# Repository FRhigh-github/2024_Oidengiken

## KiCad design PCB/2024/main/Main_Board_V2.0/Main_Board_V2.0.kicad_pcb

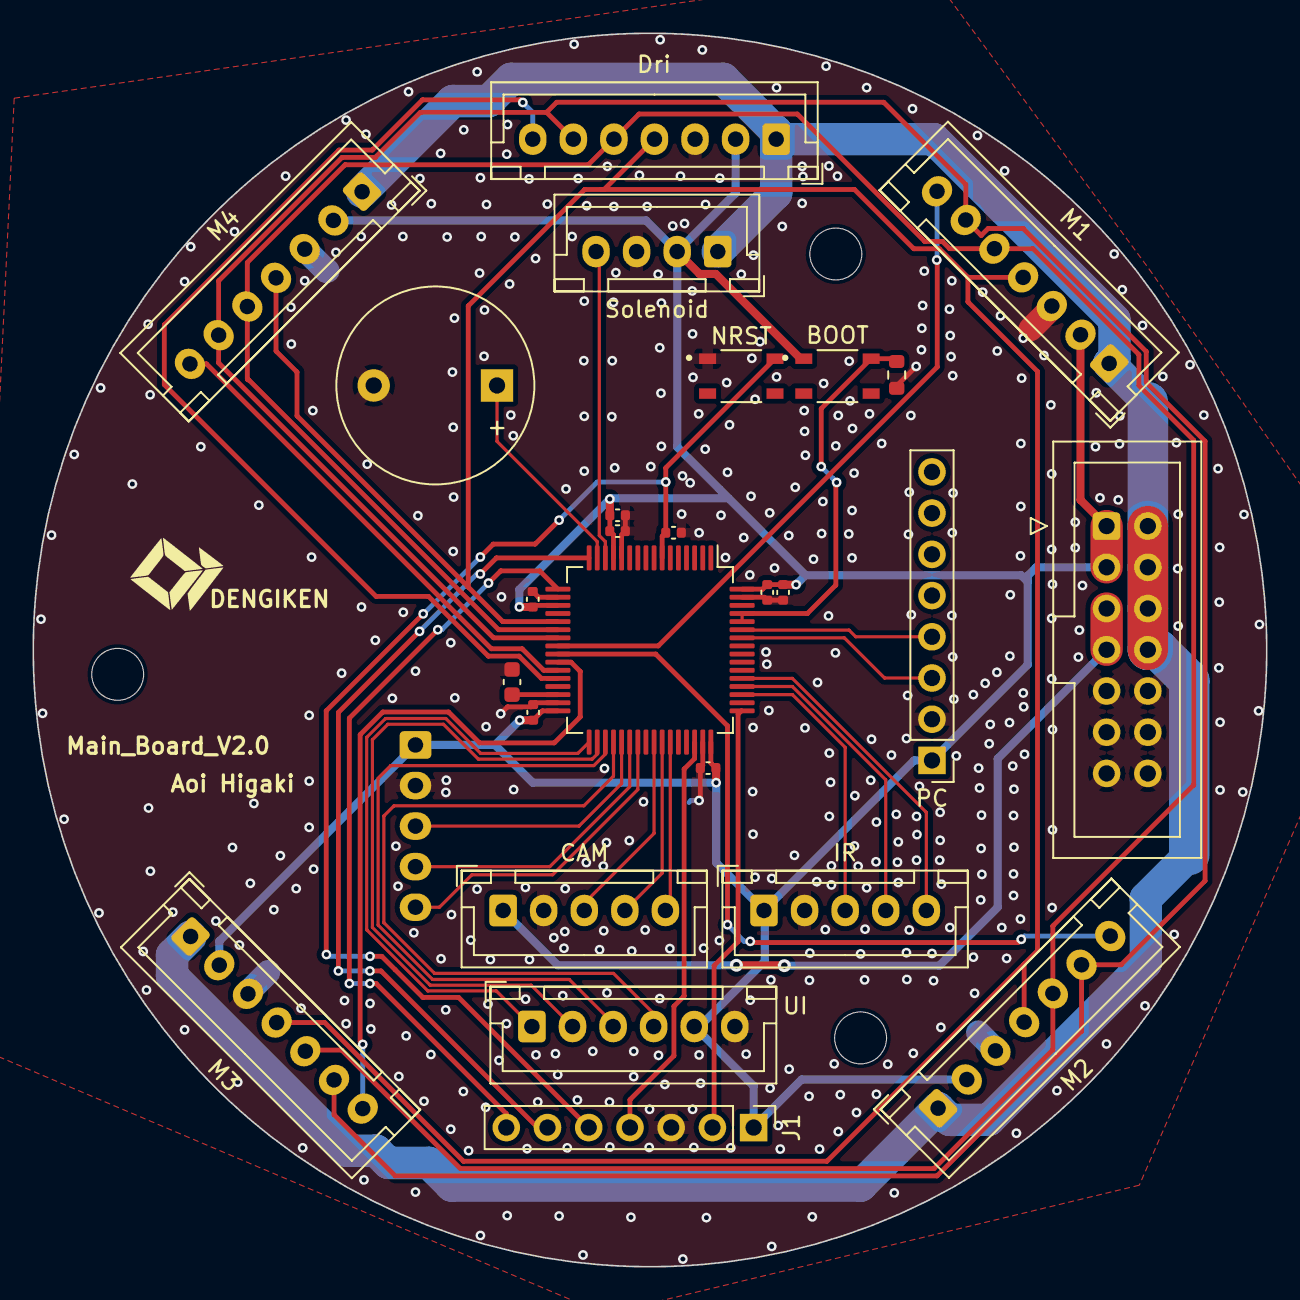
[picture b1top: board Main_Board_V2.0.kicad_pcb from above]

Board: 2 copper layers, 76.0 x 76.0 mm, 27 parts (1 on the bottom side), 36 nets.

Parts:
BOOT: SW_Push; SW_SKRPABE010
BZ1: Buzzer; Buzzer_12x9.5RM7.6
C1, C3, C4, C6, C8, C9: 0.1u; C_0402_1005Metric
C2: 2.2u; C_0603_1608Metric
C5, C7: 1u; C_0402_1005Metric
CAM: CAM; JST_XH_B5B-XH-A_1x05_P2.50mm_Vertical
Dri: dri; JST_XH_B7B-XH-A_1x07_P2.50mm_Vertical
IR: IR; JST_XH_B5B-XH-A_1x05_P2.50mm_Vertical
J1: Conn_01x07_Pin; PinHeader_1x07_P2.54mm_Vertical
J11: 電源基盤; IDC-Header_2x07_P2.54mm_Vertical
Line: Line; JST_XH_B5B-XH-A_1x05_P2.50mm_Vertical
M1: M1; JST_XH_B7B-XH-A_1x07_P2.50mm_Vertical
M2: M2; JST_XH_B7B-XH-A_1x07_P2.50mm_Vertical
M3: M3; JST_XH_B7B-XH-A_1x07_P2.50mm_Vertical
M4: M4; JST_XH_B7B-XH-A_1x07_P2.50mm_Vertical
NRST: SW_Push; SW_SKRPABE010
PC: Conn_01x08_Pin; PinHeader_1x08_P2.54mm_Vertical
R1: 10k; R_0603_1608Metric
Solenoid: Solenoid; JST_XH_B4B-XH-A_1x04_P2.50mm_Vertical
U1: STM32F446RETx; LQFP-64_10x10mm_P0.5mm
UI: UI; JST_XH_B6B-XH-A_1x06_P2.50mm_Vertical

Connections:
+5V: CAM.1, J11.5, J11.7
+12V: Dri.1, J11.2, J11.4, J11.6, J11.8, M1.1, M2.1, M3.1, M4.1, Solenoid.1
BOOT: BOOT.2, R1.1, U1.60 (BOOT0), U1.61 (PB8)
Buzzer: BZ1.1 (-), U1.15 (PA1)
I2C_SCL: PC.3, U1.58 (PB6)
I2C_SDA: PC.4, U1.59 (PB7)
NRST: C9.1, J1.5, NRST.2, U1.7 (NRST)
SPI1_CS0: M1.7, U1.24 (PC4)
SPI1_CS1: M2.7, U1.25 (PC5)
SPI1_CS2: M3.7, U1.26 (PB0)
SPI1_CS3: M4.7, U1.27 (PB1)
SPI1_CS4: Dri.7, U1.28 (PB2)
SPI1_MISO: Dri.5, M1.5, M2.5, M3.5, M4.5, U1.22 (PA6)
SPI1_MOSI: Dri.6, M1.6, M2.6, M3.6, M4.6, U1.23 (PA7)
SPI1_SCK: Dri.4, M1.4, M2.4, M3.4, M4.4, U1.21 (PA5)
ST_SW: U1.33 (PB12), UI.1
SWCLK: J1.2, U1.49 (PA14)
SWDIO: J1.4, U1.46 (PA13)
Solenoid: Solenoid.4, U1.14 (PA0)
UI_1: U1.34 (PB13), UI.2
UI_2: U1.35 (PB14), UI.3
UI_3: U1.36 (PB15), UI.4
USART1_CK: CAM.3, U1.41 (PA8)
USART1_RX: CAM.5, U1.43 (PA10)
USART1_TX: CAM.4, U1.42 (PA9)
USART2_RX: J1.7, U1.17 (PA3)
USART2_TX: J1.6, U1.16 (PA2)
USART3_CK: IR.5, U1.53 (PC12)
USART3_RX: IR.4, U1.52 (PC11)
USART3_TX: IR.3, U1.51 (PC10)
USART6_CK: Line.5, U1.39 (PC8)
USART6_RX: Line.4, U1.38 (PC7)
USART6_TX: Line.3, U1.37 (PC6)
VCAP: C2.1, U1.30 (VCAP_1)
VDD1: BOOT.1, C1.1, C3.1, C4.1, C5.1, C6.1, C7.1, C8.1, Dri.2, IR.1, J1.1, J11.1, J11.3, Line.1, M1.2, M2.2, M3.2, M4.2, PC.1, Solenoid.2, U1.13 (VDDA), U1.19 (VDD), U1.32 (VDD), U1.48 (VDD), U1.64 (VDD), UI.5
VSSA: BZ1.2 (+), C1.2, C2.2, C3.2, C4.2, C5.2, C6.2, C7.2, C8.2, C9.2, CAM.2, Dri.3, IR.2, J1.3, J11.9, J11.10, J11.11, J11.12, J11.13, J11.14, Line.2, M1.3, M2.3, M3.3, M4.3, NRST.1, PC.2, R1.2, Solenoid.3, U1.12 (VSSA), U1.18 (VSS), U1.31 (VSS), U1.47 (VSS), U1.63 (VSS), UI.6

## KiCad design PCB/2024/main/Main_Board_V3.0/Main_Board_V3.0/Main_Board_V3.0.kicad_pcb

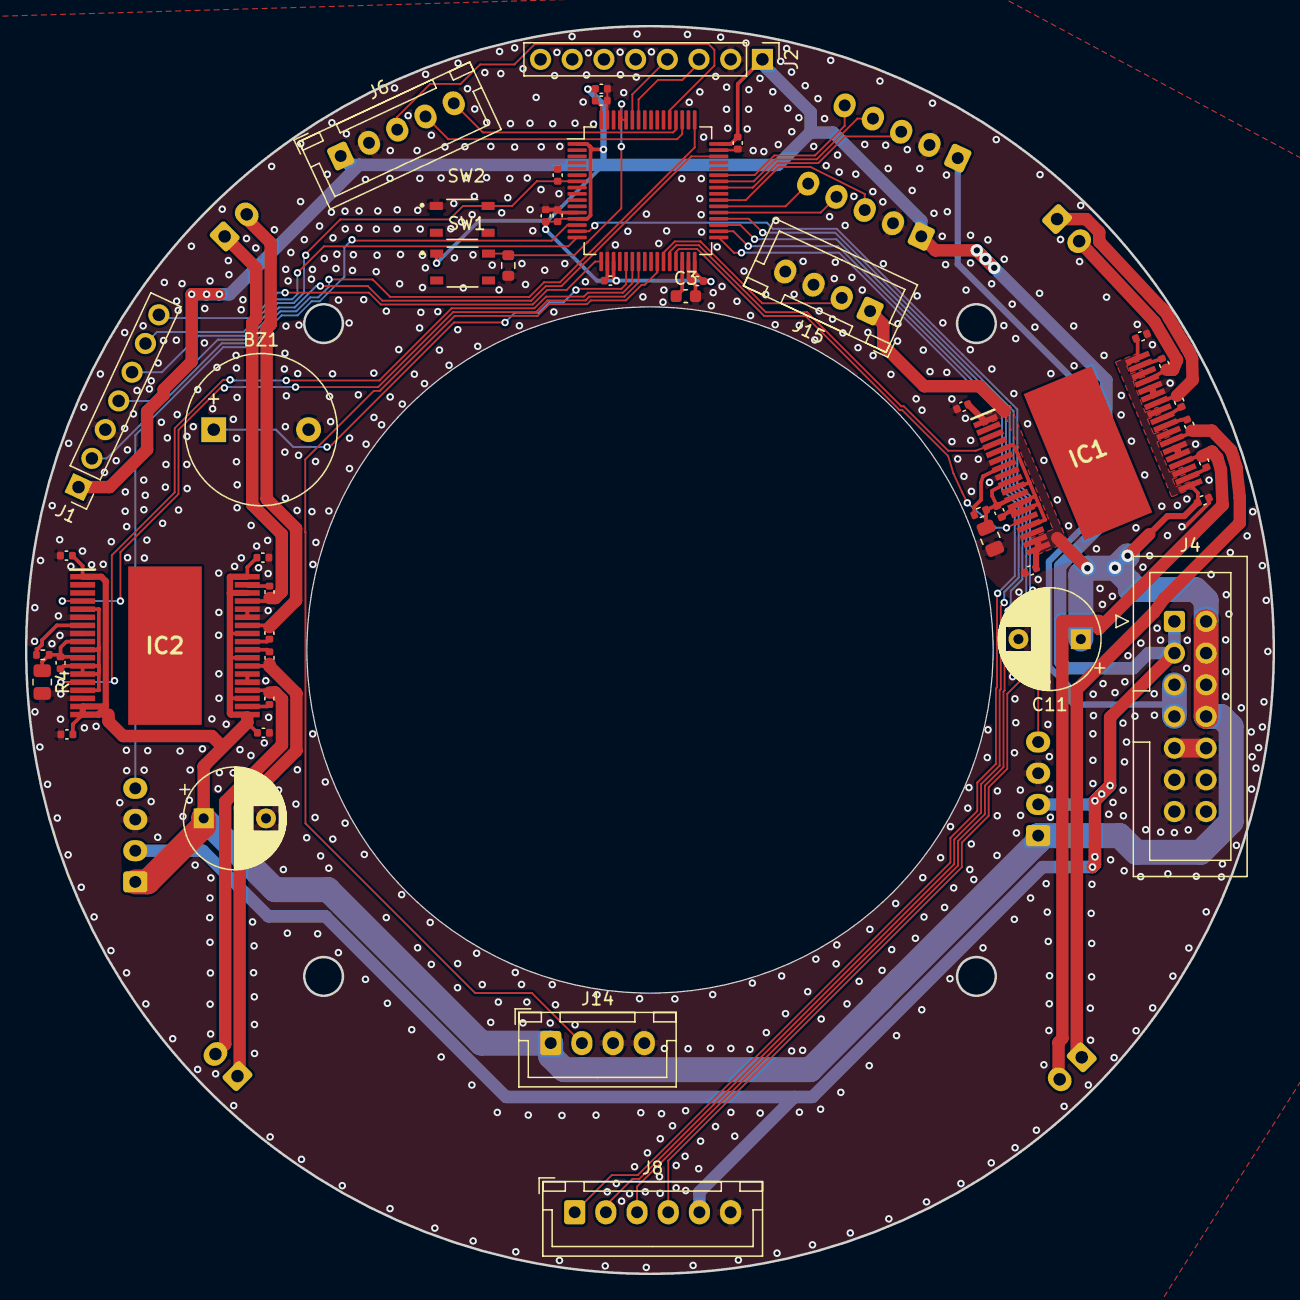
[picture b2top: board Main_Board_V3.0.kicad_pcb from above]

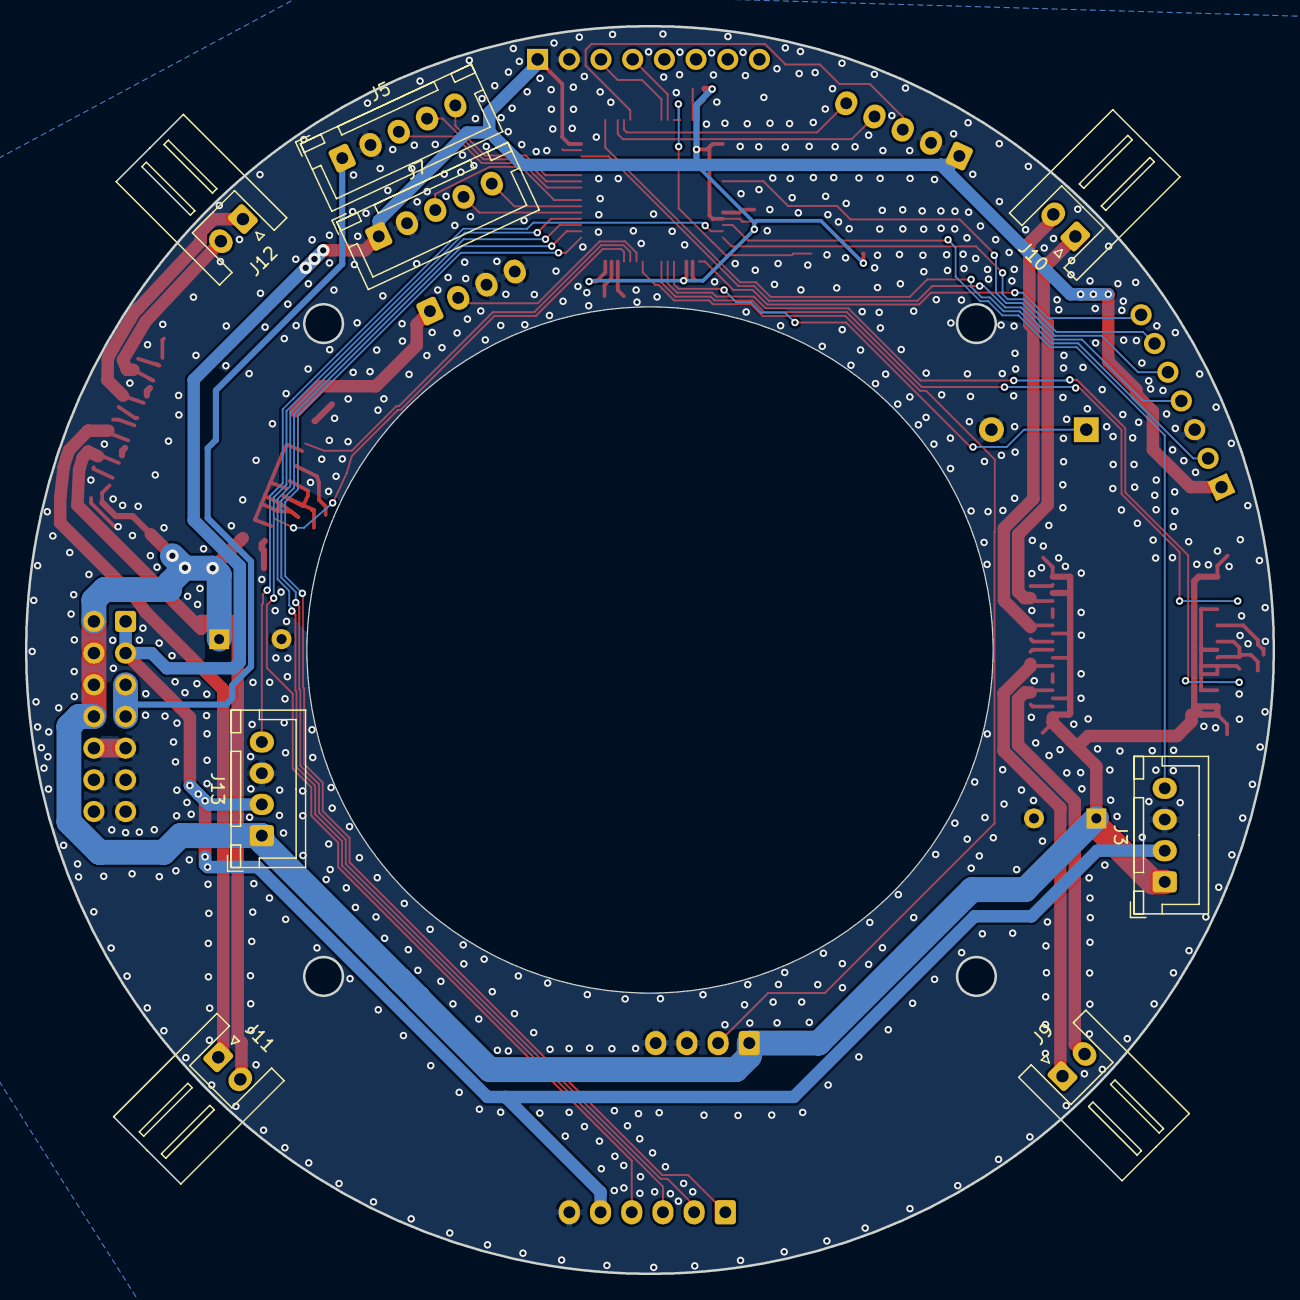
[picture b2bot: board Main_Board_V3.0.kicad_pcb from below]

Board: 2 copper layers, 100.0 x 100.0 mm, 55 parts (8 on the bottom side), 57 nets.

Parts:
BZ1: Buzzer; Buzzer_12x9.5RM7.6
C1, C2, C4, C6, C8, C9, C15, C16, C17, C18, C19, C20, C21, C22, C23, C24: 0.1u; C_0402_1005Metric
C3: 2.2u; C_0603_1608Metric
C5, C7, C10, C12, C13, C14, C26, C27, C28, C29: 1u; C_0402_1005Metric
C11, C25: 330; CP_Radial_D8.0mm_P5.00mm
IC1, IC2: DRV8432DKDR; SOP65P1420X360-37N
J1: Conn_01x07_Pin; PinHeader_1x07_P2.54mm_Vertical
J2: Conn_01x08_Pin; PinHeader_1x08_P2.54mm_Vertical
J3, J13: Solenoid; JST_XH_B4B-XH-A_1x04_P2.50mm_Vertical
J4: 電源基盤; IDC-Header_2x07_P2.54mm_Vertical
J5: CAM; JST_XH_B5B-XH-A_1x05_P2.50mm_Vertical
J6: IR; JST_XH_B5B-XH-A_1x05_P2.50mm_Vertical
J7: Line; JST_XH_B5B-XH-A_1x05_P2.50mm_Vertical
J8: UI; JST_XH_B6B-XH-A_1x06_P2.50mm_Vertical
J9, J10, J11, J12: Conn_01x02_Pin; JST_XH_S2B-XH-A_1x02_P2.50mm_Horizontal
J14, J15: Conn_01x04_Pin; JST_XH_B4B-XH-A_1x04_P2.50mm_Vertical
R1: 10k; R_0603_1608Metric
R2, R4: 1.0; R_0805_2012Metric
R3, R5: 47K; R_0402_1005Metric
SW1, SW2: SW_Push; SW_SKRPABE010
U1: STM32F446RETx; LQFP-64_10x10mm_P0.5mm

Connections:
+5V: J4.5, J4.7, J5.1
BOOT: R1.1, SW1.2, U1.60 (BOOT0), U1.61 (PB8)
BST1_A: C16.2, IC1.33 (OUT_A), J12.2
BST1_B: C17.2, IC1.30 (OUT_B), J12.1
BST2_A: C19.2, IC1.25 (OUT_C), J11.1
BST2_B: C18.2, IC1.22 (OUT_D), J11.2
BST3_A: C21.2, IC2.33 (OUT_A), J10.1
BST3_B: C22.2, IC2.30 (OUT_B), J10.2
BST4_A: C24.2, IC2.25 (OUT_C), J9.1
BST4_B: C23.2, IC2.22 (OUT_D), J9.2
Buzzer: BZ1.1 (-), U1.21 (PA5)
I2C_SCL: J2.3, U1.58 (PB6)
I2C_SDA: J2.4, U1.59 (PB7)
NRST: C9.1, J1.5, SW2.2, U1.7 (NRST)
unnamed: C16.1, IC1.35 (BST_A)
unnamed: C17.1, IC1.28 (BST_B)
unnamed: C19.1, IC1.27 (BST_C)
unnamed: C18.1, IC1.20 (BST_D)
unnamed: IC1.7 (OC_ADJ), R3.1
unnamed: C21.1, IC2.35 (BST_A)
unnamed: C22.1, IC2.28 (BST_B)
unnamed: C24.1, IC2.27 (BST_C)
unnamed: C23.1, IC2.20 (BST_D)
unnamed: IC2.7 (OC_ADJ), R5.1
PWM1: IC1.4 (PWM_A), U1.28 (PB2)
PWM2: IC1.14 (PWM_C), U1.29 (PB10)
PWM3: IC2.4 (PWM_A), U1.23 (PA7)
PWM4: IC2.14 (PWM_C), U1.22 (PA6)
PWM5: J14.2, U1.26 (PB0)
PWM6: J15.2, U1.27 (PB1)
ST_SW: J8.1, U1.33 (PB12)
SWCLK: J1.2, U1.49 (PA14)
SWDIO: J1.4, U1.46 (PA13)
Solenoid1: J3.4, U1.14 (PA0)
Solenoid2: J13.4, U1.15 (PA1)
UI_1: J8.2, U1.34 (PB13)
UI_2: J8.3, U1.35 (PB14)
UI_3: J8.4, U1.36 (PB15)
USART1_CK: J5.3, U1.41 (PA8)
USART1_RX: J5.5, U1.43 (PA10)
USART1_TX: J5.4, U1.42 (PA9)
USART2_RX: J1.7, U1.17 (PA3)
USART2_TX: J1.6, U1.16 (PA2)
USART3_CK: J6.3, U1.53 (PC12)
USART3_RX: J6.5, U1.52 (PC11)
USART3_TX: J6.4, U1.51 (PC10)
USART6_CK: J7.3, U1.39 (PC8)
USART6_RX: J7.5, U1.38 (PC7)
USART6_TX: J7.4, U1.37 (PC6)
VCAP: C3.1, U1.30 (VCAP_1)
VCC: C10.1, C11.1, C12.1, C13.1, C14.1, C25.1, C26.1, C27.1, C28.1, C29.1, IC1.1 (GVDD_B), IC1.17 (VDD), IC1.18 (GVDD_C), IC1.19 (GVDD_D), IC1.21 (PVDD_D), IC1.26 (PVDD_C), IC1.29 (PVDD_B), IC1.34 (PVDD_A), IC1.36 (GVDD_A), IC2.1 (GVDD_B), IC2.17 (VDD), IC2.18 (GVDD_C), IC2.19 (GVDD_D), IC2.21 (PVDD_D), IC2.26 (PVDD_C), IC2.29 (PVDD_B), IC2.34 (PVDD_A), IC2.36 (GVDD_A), J3.1, J4.2, J4.4, J4.6, J4.8, J13.1, J14.1, J15.1
VDD1: C1.1, C2.1, C4.1, C5.1, C6.1, C7.1, C8.1, J1.1, J2.1, J3.2, J4.1, J4.3, J6.1, J7.1, J8.5, J13.2, SW1.1, U1.1 (VBAT), U1.13 (VDDA), U1.19 (VDD), U1.32 (VDD), U1.48 (VDD), U1.64 (VDD)
VDDAB: C15.1, IC1.5 (~RESET_AB), IC1.10 (VREG), IC1.12 (M2), IC1.13 (M1), IC1.15 (~RESET_CD)
VDDCD: C20.1, IC2.5 (~RESET_AB), IC2.10 (VREG), IC2.12 (M2), IC2.13 (M1), IC2.15 (~RESET_CD)
VSSA: BZ1.2 (+), C1.2, C2.2, C3.2, C4.2, C5.2, C6.2, C7.2, C8.2, C9.2, C10.2, C11.2, C12.2, C13.2, C14.2, C25.2, C26.2, C27.2, C28.2, C29.2, IC1.6 (PWM_B), IC1.8 (GND), IC1.16 (PWM_D), IC1.23 (GND_D), IC1.24 (GND_C), IC1.31 (GND_B), IC1.32 (GND_A), IC2.6 (PWM_B), IC2.8 (GND), IC2.16 (PWM_D), IC2.23 (GND_D), IC2.24 (GND_C), IC2.31 (GND_B), IC2.32 (GND_A), J1.3, J2.2, J3.3, J4.9, J4.10, J4.11, J4.12, J4.13, J4.14, J5.2, J6.2, J7.2, J8.6, J13.3, J14.3, J14.4, J15.3, J15.4, R1.2, R2.2, R4.2, SW2.1, U1.12 (VSSA), U1.18 (VSS), U1.31 (VSS), U1.47 (VSS), U1.63 (VSS)
VSSAB: C15.2, IC1.9 (AGND), IC1.11 (M3), R2.1, R3.2
VSSCD: C20.2, IC2.9 (AGND), IC2.11 (M3), R4.1, R5.2

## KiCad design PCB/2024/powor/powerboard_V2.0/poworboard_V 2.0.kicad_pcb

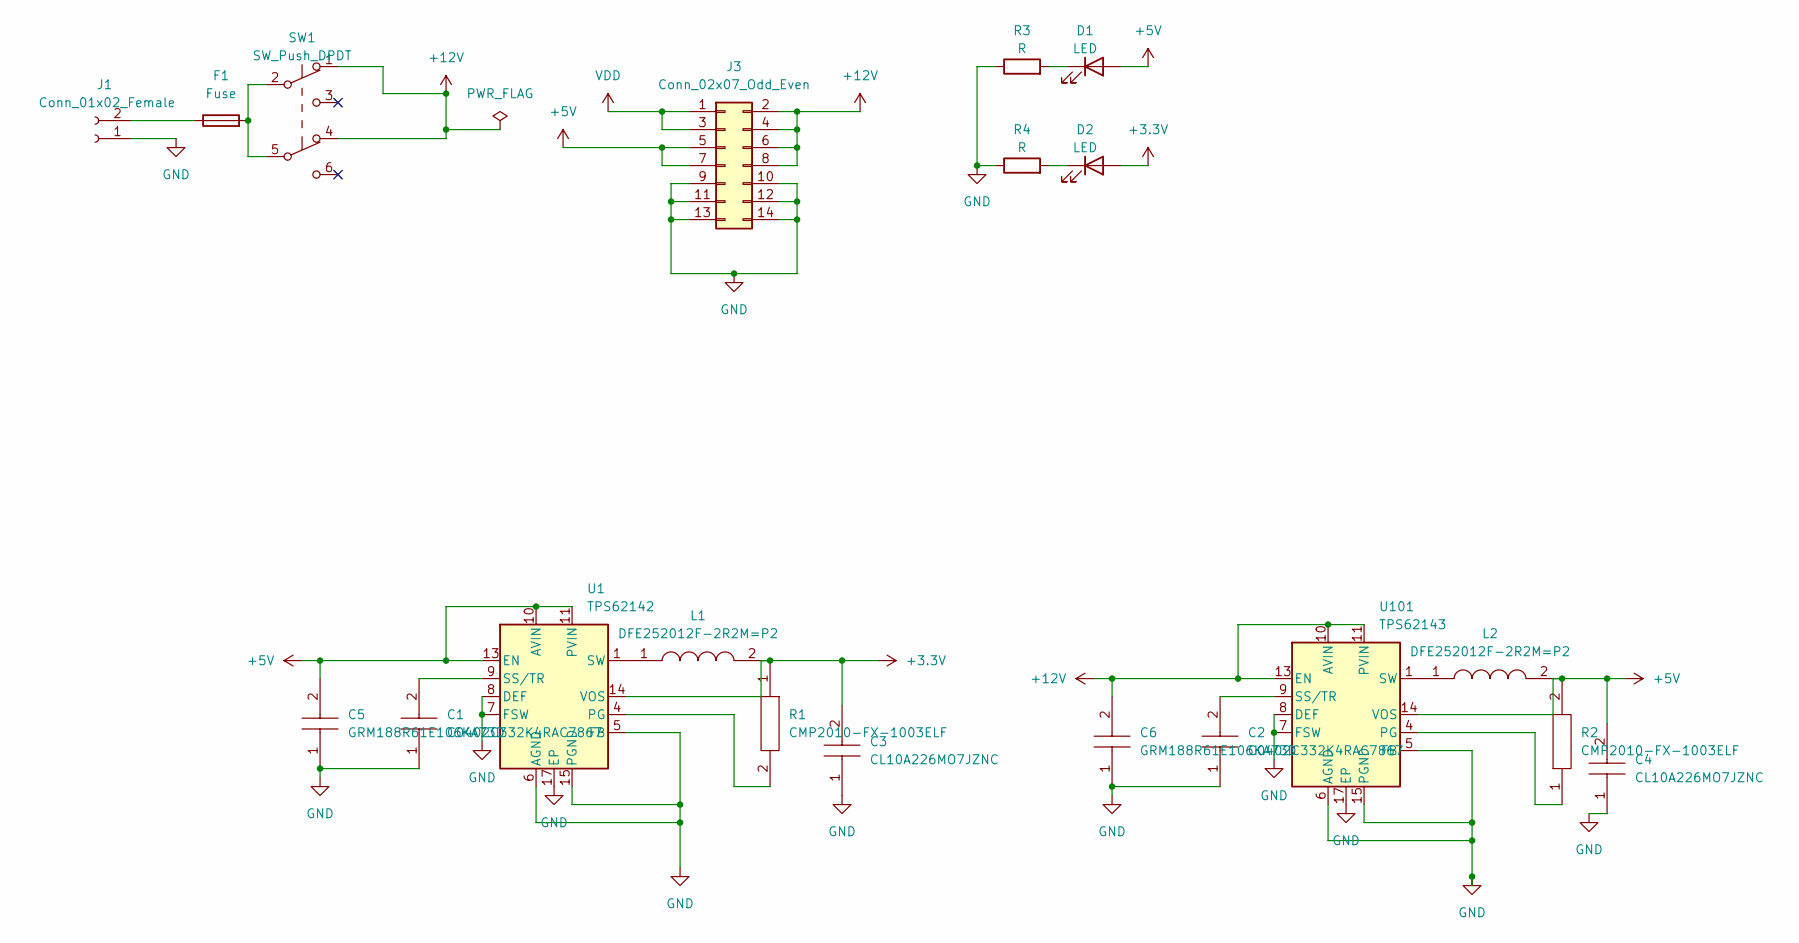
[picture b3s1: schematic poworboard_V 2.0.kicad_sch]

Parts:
C1, C2: C0402C332K4RAC7867; C0402; Manufacturer_Part_Number C0402C332K4RAC7867
C3, C4: CL10A226MO7JZNC; CAPC1608X80N; Manufacturer_Part_Number CL10A226MO7JZNC
C5, C6: GRM188R61E106KA73D; CAPC1608X90N; Manufacturer_Part_Number GRM188R61E106KA73D
D1, D2: LED; LED_0603_1608Metric
F1: Fuse; Fuseholder_Cylinder-5x20mm_Schurter_0031_8201_Horizontal_Op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
J1: Conn_01x02_Female; TerminalBlock_bornier-2_P5.08mm
J3: Conn_02x07_Odd_Even; IDC-Header_2x07_P2.54mm_Vertical
L1, L2: DFE252012F-2R2M=P2; DFE2HCAH1R0MJ0L; Manufacturer_Part_Number DFE252012F-2R2M=P2
R1, R2: CMP2010-FX-1003ELF; RESC5025X70N; Manufacturer_Part_Number CMP2010-FX-1003ELF
R3, R4: R; R_0603_1608Metric
SW1: SW_Push_DPDT; Toggle
U1: TPS62142; VQFN-16-1EP_3x3mm_P0.5mm_EP1.68x1.68mm_ThermalVias
U101: TPS62143; VQFN-16-1EP_3x3mm_P0.5mm_EP1.68x1.68mm_ThermalVias

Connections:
+3.3V: C3.2, D2.2 (A), L1.2, R1.1, U1.14 (VOS)
+5V: C4.2, C5.2, D1.2 (A), J3.5, J3.7, L2.2, R2.2, U1.10 (AVIN), U1.11 (PVIN), U1.12 (PVIN), U1.13 (EN), U101.14 (VOS)
+12V: C6.2, J3.2, J3.4, J3.6, J3.8, SW1.1 (A), SW1.4 (A), U101.10 (AVIN), U101.11 (PVIN), U101.12 (PVIN), U101.13 (EN)
GND: C1.1, C2.1, C3.1, C4.1, C5.1, C6.1, J1.1, J3.9, J3.10, J3.11, J3.12, J3.13, J3.14, R3.1, R4.1, U1.5 (FB), U1.6 (AGND), U1.7 (FSW), U1.8 (DEF), U1.15 (PGND), U1.16 (PGND), U1.17 (EP), U101.5 (FB), U101.6 (AGND), U101.7 (FSW), U101.8 (DEF), U101.15 (PGND), U101.16 (PGND), U101.17 (EP)
unnamed: D1.1 (K), R3.2
unnamed: D2.1 (K), R4.2
unnamed: F1.2, SW1.2 (B), SW1.5 (B)
unnamed: F1.1, J1.2
unnamed: L1.1, U1.1 (SW), U1.2 (SW), U1.3 (SW)
unnamed: L2.1, U101.1 (SW), U101.2 (SW), U101.3 (SW)
unnamed: R1.2, U1.4 (PG)
unnamed: C1.2, U1.9 (SS/TR)
unnamed: R2.1, U101.4 (PG)
unnamed: C2.2, U101.9 (SS/TR)
VDD: J3.1, J3.3

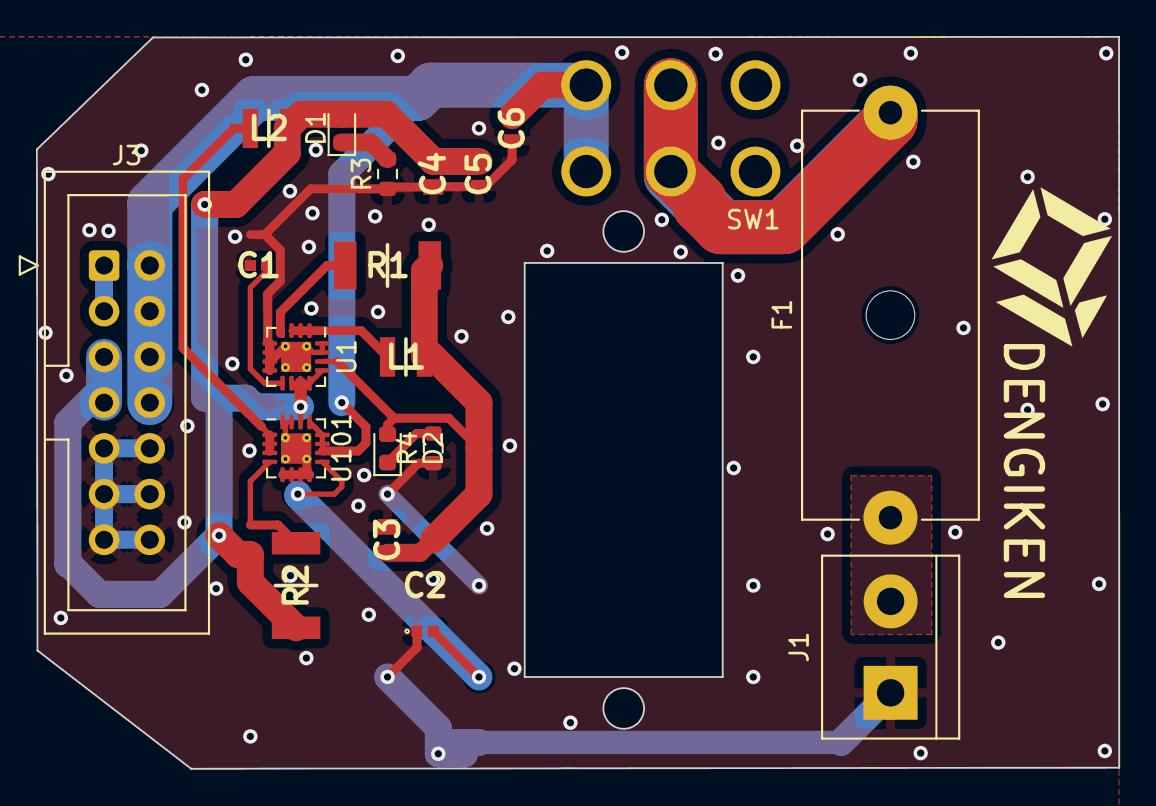
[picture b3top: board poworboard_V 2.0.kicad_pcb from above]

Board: 2 copper layers, 60.1 x 40.7 mm, 20 parts (0 on the bottom side), 15 nets.

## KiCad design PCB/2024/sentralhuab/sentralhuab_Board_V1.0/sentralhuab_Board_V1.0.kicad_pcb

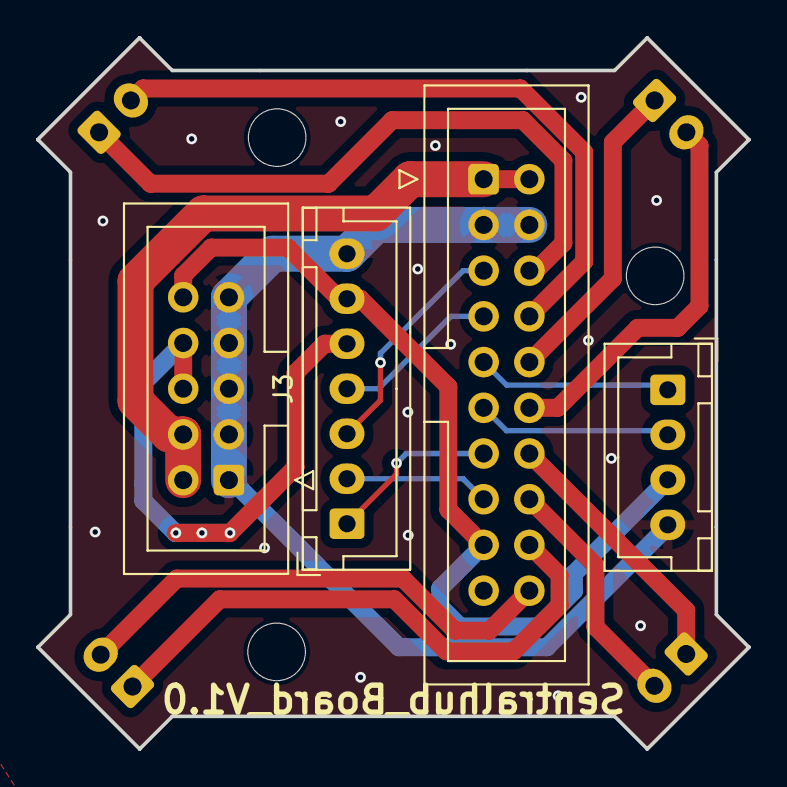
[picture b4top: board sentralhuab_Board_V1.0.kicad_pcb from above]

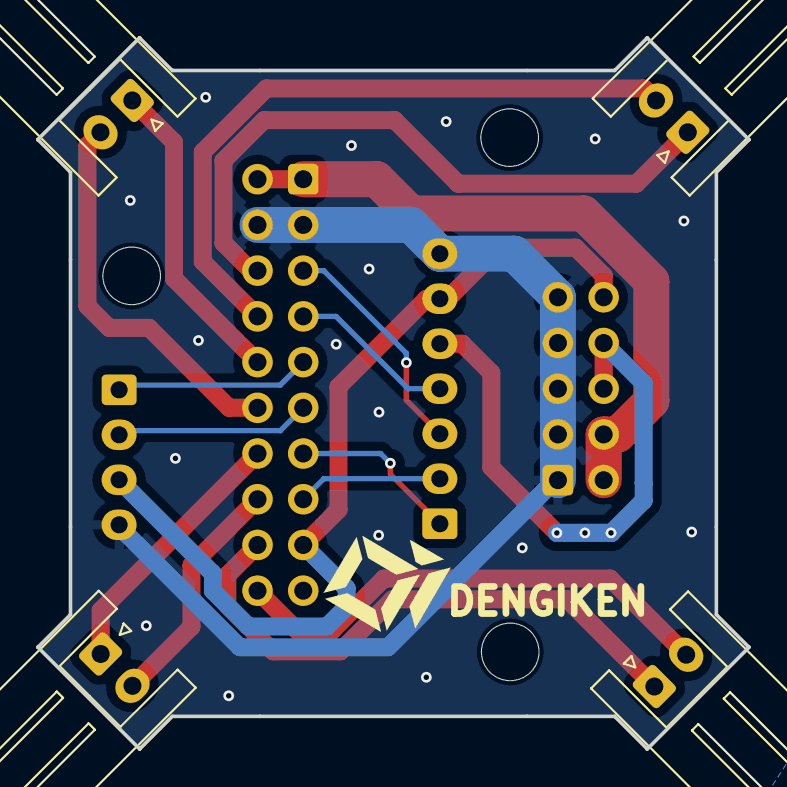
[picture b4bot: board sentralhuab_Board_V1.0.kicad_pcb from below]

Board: 2 copper layers, 39.5 x 39.5 mm, 8 parts (4 on the bottom side), 18 nets.

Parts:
J1: Conn_02x10_Odd_Even; IDC-Header_2x10_P2.54mm_Vertical
J2: Conn_01x04_Socket; JST_XH_B4B-XH-A_1x04_P2.50mm_Vertical
J3: Conn_01x07_Socket; JST_XH_B7B-XH-A_1x07_P2.50mm_Vertical
J4: Conn_02x05_Odd_Even; IDC-Header_2x05_P2.54mm_Vertical
J5, J6, J7, J8: Conn_01x02_Pin; JST_XH_S2B-XH-A_1x02_P2.50mm_Horizontal

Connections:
+5V: J3.5, J4.6, J4.8
+12V: J1.1, J1.2, J4.2, J4.4
Motor1_A: J1.20, J8.2
Motor1_B: J1.18, J8.1
Motor2_A: J1.16, J7.2
Motor2_B: J1.14, J7.1
Motor3_A: J1.12, J6.2
Motor3_B: J1.10, J6.1
Motor4_A: J1.8, J5.2
Motor4_B: J1.6, J5.1
UART4_RX_OpenMV: J1.15, J3.2
UART4_TX_OpenMV: J1.13, J3.1
UART5_RX_Angel: J1.11, J2.2
UART5_TX_Angel: J1.9, J2.1
USART1_RX_IR: J1.7, J3.4
USART1_TX_IR: J1.5, J3.3
VDD: J1.17, J2.3, J3.6, J4.10
VSS: J1.3, J1.4, J2.4, J3.7, J4.1, J4.3, J4.5, J4.7, J4.9
